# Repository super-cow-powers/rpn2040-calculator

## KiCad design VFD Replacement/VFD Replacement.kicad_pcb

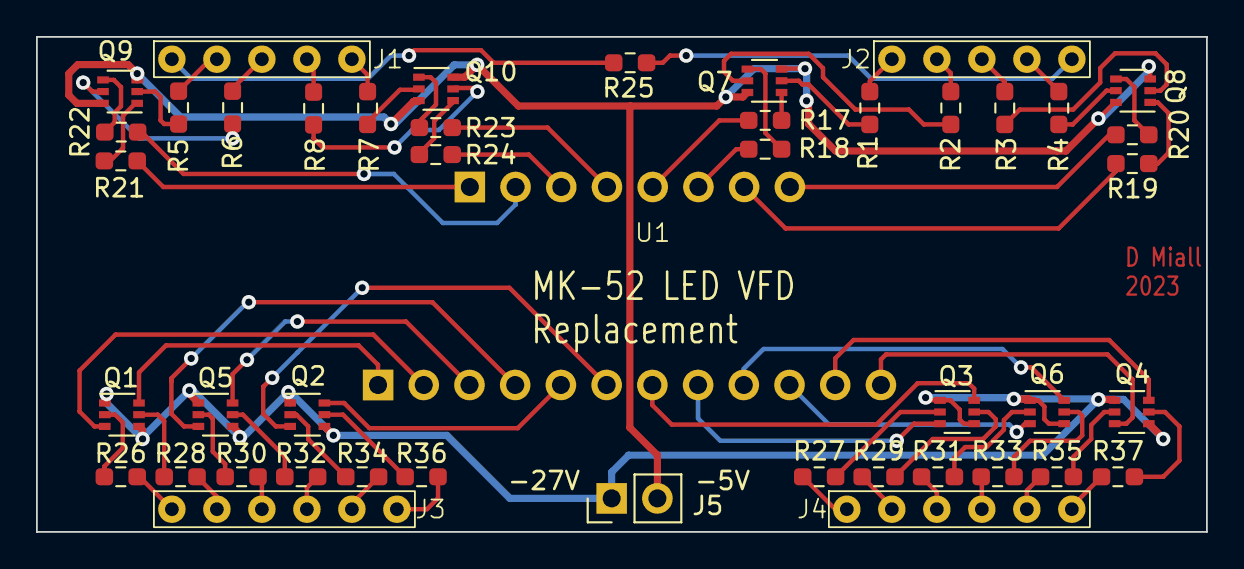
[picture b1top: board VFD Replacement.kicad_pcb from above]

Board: 2 copper layers, 65.0 x 27.5 mm, 45 parts (0 on the bottom side), 72 nets.

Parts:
J1, J2: Conn_01x05_Pin; Conn_1x05 2.5mm
J3, J4: Conn_01x06_Pin; Conn_1x06 2.5mm
J5: Conn_01x02_Pin; PinHeader_1x02_P2.54mm_Vertical
Q1, Q2, Q3, Q4, Q5, Q6, Q7, Q8, Q9, Q10: MMDT2222A; SOT-363_SC-70-6
R1, R2, R3, R4, R5, R6, R7, R8, R25: 12k; R_0603_1608Metric_Pad0.98x0.95mm_HandSolder
R17, R18, R19, R20, R21, R22, R23, R24: 2k4; R_0603_1608Metric_Pad0.98x0.95mm_HandSolder
R26, R27, R28, R29, R30, R31, R32, R33, R34, R35, R36, R37: 56k; R_0603_1608Metric_Pad0.98x0.95mm_HandSolder
U1: display

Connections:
+22V: J5.2, Q7.3 (C2), Q7.6 (C1), Q8.3 (C2), Q8.6 (C1), Q9.3 (C2), Q9.6 (C1), Q10.3 (C2), Q10.6 (C1)
-27V: J5.1, Q1.1 (E1), Q1.4 (E2), Q2.1 (E1), Q2.4 (E2), Q3.1 (E1), Q3.4 (E2), Q4.1 (E1), Q4.4 (E2), Q5.1 (E1), Q5.4 (E2), Q6.1 (E1), Q6.4 (E2)
/A: J2.1, R1.2
/As: R17.1, U1.5 (A)
/B: J2.2, R2.1
/Bs: R18.1, U1.6 (B)
/C: J2.3, R3.1
/Cs: R19.1, U1.7 (C)
/D: J1.2, R5.1
/DP: J2.4, R4.1
/DPs: R20.1, U1.8 (DP)
/Ds: R21.1, U1.1 (D)
/E: J1.3, R6.1
/Es: R22.1, U1.2 (E)
/F: J1.5, R7.1
/Fil A: J1.1, R25.2
/Fil B: J2.5, R25.1
/Fs: R23.1, U1.4 (F)
/G: J1.4, R8.1
/G1: J3.1, R26.1
/G1s: Q1.6 (C1), U1.9 (G1)
/G2: J3.2, R28.1
/G2s: Q1.3 (C2), U1.10 (G2)
/G3: J3.3, R30.1
/G3s: Q5.6 (C1), U1.11 (G3)
/G4: J3.4, R32.1
/G4s: Q5.3 (C2), U1.12 (G4)
/G5: J3.5, R34.1
/G5s: Q2.6 (C1), U1.13 (G5)
/G6: J3.6, R36.1
/G6s: Q2.3 (C2), U1.14 (G6)
/G7: J4.1, R27.1
/G7s: Q3.6 (C1), U1.15 (G7)
/G8: J4.2, R29.1
/G8s: Q3.3 (C2), U1.16 (G8)
/G9: J4.3, R31.1
/G9s: Q6.6 (C1), U1.17 (G9)
/G10: J4.4, R33.1
/G10s: Q6.3 (C2), U1.18 (G10)
/G11: J4.5, R35.1
/G11s: Q4.6 (C1), U1.19 (G11)
/G12: J4.6, R37.1
/G12s: Q4.3 (C2), U1.20 (G12)
/Gs: R24.1, U1.3 (G)
unnamed: Q1.2 (B1), R26.2
unnamed: Q1.5 (B2), R28.2
unnamed: Q2.2 (B1), R34.2
unnamed: Q2.5 (B2), R36.2
unnamed: Q3.2 (B1), R27.2
unnamed: Q3.5 (B2), R29.2
unnamed: Q4.2 (B1), R35.2
unnamed: Q4.5 (B2), R37.2
unnamed: Q5.2 (B1), R30.2
unnamed: Q5.5 (B2), R32.2
unnamed: Q6.2 (B1), R31.2
unnamed: Q6.5 (B2), R33.2
unnamed: Q7.2 (B1), R1.1
unnamed: Q7.1 (E1), R17.2
unnamed: Q7.5 (B2), R2.2
unnamed: Q7.4 (E2), R18.2
unnamed: Q8.2 (B1), R3.2
unnamed: Q8.1 (E1), R19.2
unnamed: Q8.5 (B2), R4.2
unnamed: Q8.4 (E2), R20.2
unnamed: Q9.2 (B1), R5.2
unnamed: Q9.1 (E1), R21.2
unnamed: Q9.5 (B2), R6.2
unnamed: Q9.4 (E2), R22.2
unnamed: Q10.2 (B1), R7.2
unnamed: Q10.1 (E1), R23.2
unnamed: Q10.5 (B2), R8.2
unnamed: Q10.4 (E2), R24.2

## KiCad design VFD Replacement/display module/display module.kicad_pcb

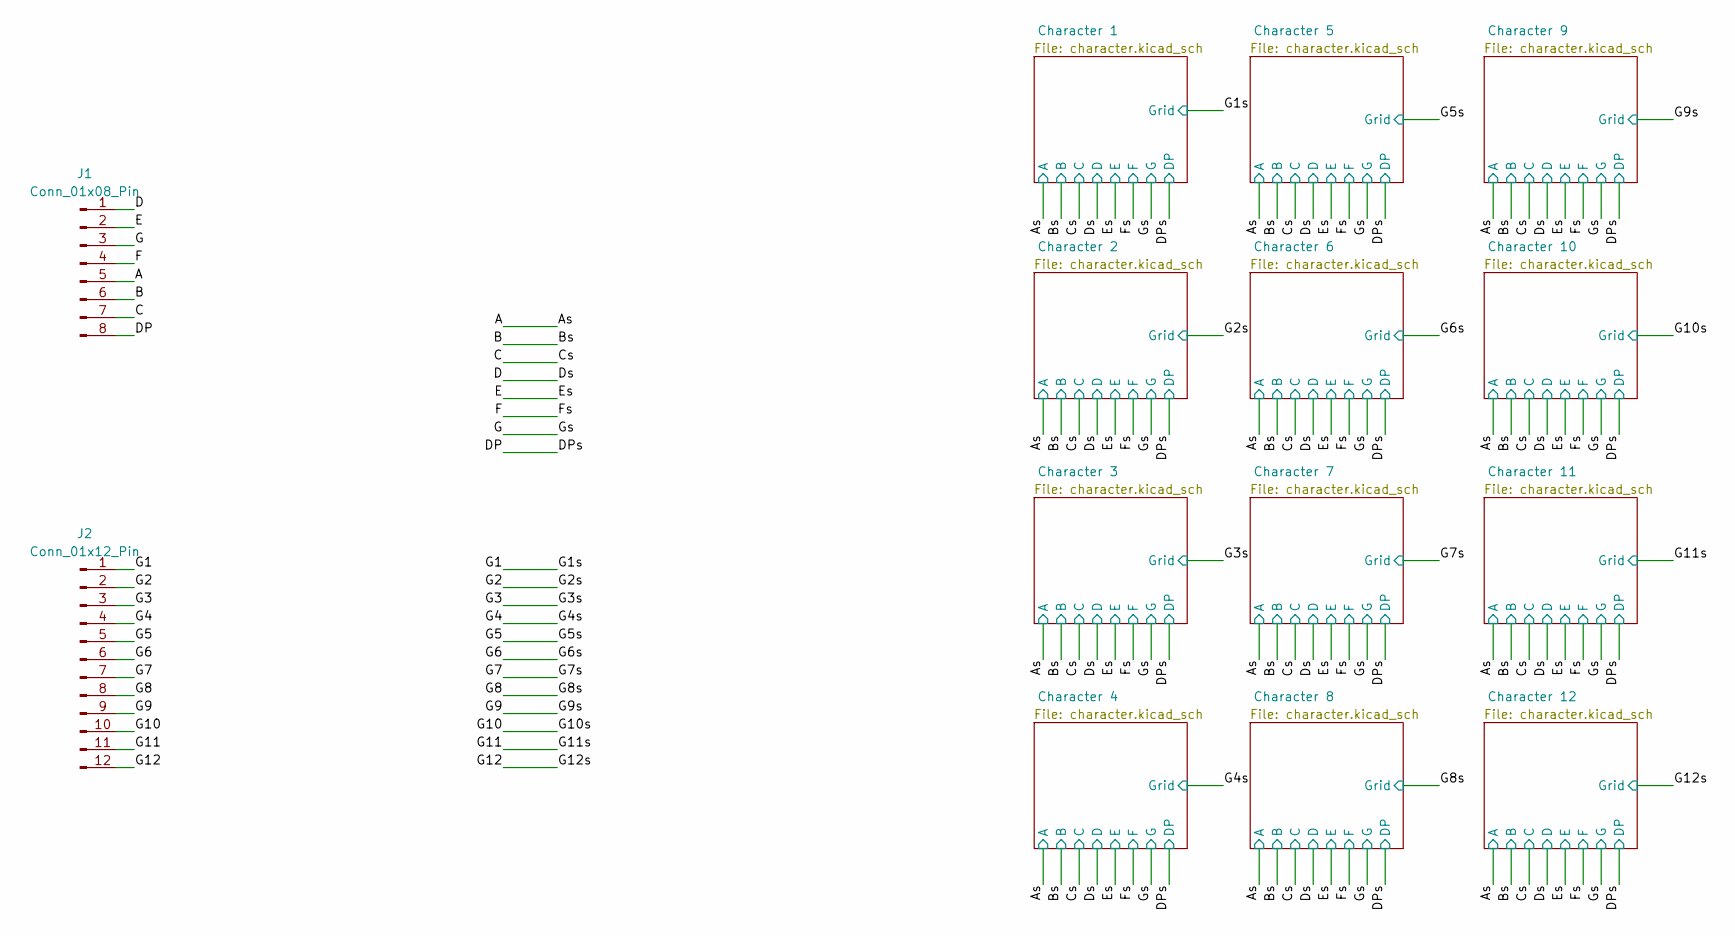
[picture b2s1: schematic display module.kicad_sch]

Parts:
J1: Conn_01x08_Pin; PinHeader_1x08_P2.54mm_Vertical
J2: Conn_01x12_Pin; PinHeader_1x12_P2.54mm_Vertical

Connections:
/A: J1.5; also elsewhere on the board
/B: J1.6; also elsewhere on the board
/C: J1.7; also elsewhere on the board
/D: J1.1; also elsewhere on the board
/DP: J1.8; also elsewhere on the board
/E: J1.2; also elsewhere on the board
/F: J1.4; also elsewhere on the board
/G: J1.3; also elsewhere on the board
/G1: J2.1; also elsewhere on the board
/G2: J2.2; also elsewhere on the board
/G3: J2.3; also elsewhere on the board
/G4: J2.4; also elsewhere on the board
/G5: J2.5; also elsewhere on the board
/G6: J2.6; also elsewhere on the board
/G7: J2.7; also elsewhere on the board
/G8: J2.8; also elsewhere on the board
/G9: J2.9; also elsewhere on the board
/G10: J2.10; also elsewhere on the board
/G11: J2.11; also elsewhere on the board
/G12: J2.12; also elsewhere on the board

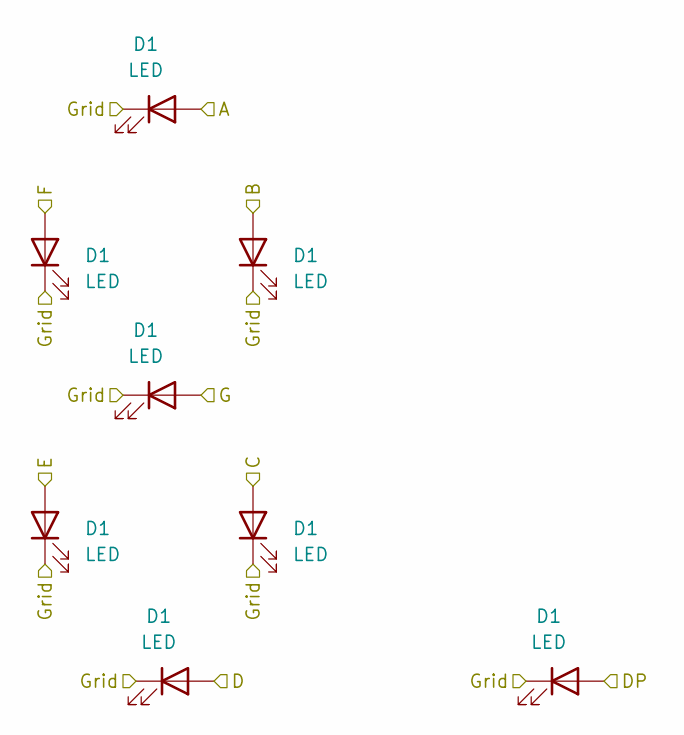
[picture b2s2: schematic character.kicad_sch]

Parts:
D1: LED; LED_0402_1005Metric

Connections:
/A: D1.2 (A); also elsewhere on the board
/G1: D1.1 (K); also elsewhere on the board

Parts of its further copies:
D2, D3, D4, D5, D6, D7, D8, D9, D10, D11, D12, D13, D14, D15, D16, D17, D18, D19, D20, D21, D22, D23, D24, D25, D26, D27, D28, D29, D30, D31, D32, D33, D34, D35, D36, D37, D38, D39, D40, D41, D42, D43, D44, D45, D46, D47, D48, D49, D50, D51, D52, D53, D54, D55, D56, D57, D58, D59, D60, D61, D62, D63, D64, D65, D66, D67, D68, D69, D70, D71, D72, D73, D74, D75, D76, D77, D78, D79, D80, D81, D82, D83, D84, D85, D86, D87, D88, D89, D90, D91, D92, D93, D94, D95, D96: LED; LED_0402_1005Metric

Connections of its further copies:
/A: D11.2 (A), D19.2 (A), D27.2 (A), D35.2 (A), D43.2 (A), D51.2 (A), D59.2 (A), D67.2 (A), D75.2 (A), D83.2 (A), D91.2 (A); also elsewhere on the board
/B: D6.2 (A), D14.2 (A), D22.2 (A), D30.2 (A), D38.2 (A), D46.2 (A), D54.2 (A), D62.2 (A), D70.2 (A), D78.2 (A), D86.2 (A), D94.2 (A); also elsewhere on the board
/C: D7.2 (A), D15.2 (A), D23.2 (A), D31.2 (A), D39.2 (A), D47.2 (A), D55.2 (A), D63.2 (A), D71.2 (A), D79.2 (A), D87.2 (A), D95.2 (A); also elsewhere on the board
/D: D4.2 (A), D13.2 (A), D21.2 (A), D29.2 (A), D37.2 (A), D45.2 (A), D53.2 (A), D61.2 (A), D69.2 (A), D77.2 (A), D85.2 (A), D93.2 (A); also elsewhere on the board
/DP: D8.2 (A), D16.2 (A), D24.2 (A), D32.2 (A), D40.2 (A), D48.2 (A), D56.2 (A), D64.2 (A), D72.2 (A), D80.2 (A), D88.2 (A), D96.2 (A); also elsewhere on the board
/E: D3.2 (A), D10.2 (A), D18.2 (A), D26.2 (A), D34.2 (A), D42.2 (A), D50.2 (A), D58.2 (A), D66.2 (A), D74.2 (A), D82.2 (A), D90.2 (A); also elsewhere on the board
/F: D2.2 (A), D9.2 (A), D17.2 (A), D25.2 (A), D33.2 (A), D41.2 (A), D49.2 (A), D57.2 (A), D65.2 (A), D73.2 (A), D81.2 (A), D89.2 (A); also elsewhere on the board
/G: D5.2 (A), D12.2 (A), D20.2 (A), D28.2 (A), D36.2 (A), D44.2 (A), D52.2 (A), D60.2 (A), D68.2 (A), D76.2 (A), D84.2 (A), D92.2 (A); also elsewhere on the board
/G1: D2.1 (K), D3.1 (K), D4.1 (K), D5.1 (K), D6.1 (K), D7.1 (K), D8.1 (K); also elsewhere on the board
/G2: D9.1 (K), D10.1 (K), D11.1 (K), D12.1 (K), D13.1 (K), D14.1 (K), D15.1 (K), D16.1 (K); also elsewhere on the board
/G3: D17.1 (K), D18.1 (K), D19.1 (K), D20.1 (K), D21.1 (K), D22.1 (K), D23.1 (K), D24.1 (K); also elsewhere on the board
/G4: D25.1 (K), D26.1 (K), D27.1 (K), D28.1 (K), D29.1 (K), D30.1 (K), D31.1 (K), D32.1 (K); also elsewhere on the board
/G5: D33.1 (K), D34.1 (K), D35.1 (K), D36.1 (K), D37.1 (K), D38.1 (K), D39.1 (K), D40.1 (K); also elsewhere on the board
/G6: D41.1 (K), D42.1 (K), D43.1 (K), D44.1 (K), D45.1 (K), D46.1 (K), D47.1 (K), D48.1 (K); also elsewhere on the board
/G7: D49.1 (K), D50.1 (K), D51.1 (K), D52.1 (K), D53.1 (K), D54.1 (K), D55.1 (K), D56.1 (K); also elsewhere on the board
/G8: D57.1 (K), D58.1 (K), D59.1 (K), D60.1 (K), D61.1 (K), D62.1 (K), D63.1 (K), D64.1 (K); also elsewhere on the board
/G9: D65.1 (K), D66.1 (K), D67.1 (K), D68.1 (K), D69.1 (K), D70.1 (K), D71.1 (K), D72.1 (K); also elsewhere on the board
/G10: D73.1 (K), D74.1 (K), D75.1 (K), D76.1 (K), D77.1 (K), D78.1 (K), D79.1 (K), D80.1 (K); also elsewhere on the board
/G11: D81.1 (K), D82.1 (K), D83.1 (K), D84.1 (K), D85.1 (K), D86.1 (K), D87.1 (K), D88.1 (K); also elsewhere on the board
/G12: D89.1 (K), D90.1 (K), D91.1 (K), D92.1 (K), D93.1 (K), D94.1 (K), D95.1 (K), D96.1 (K); also elsewhere on the board

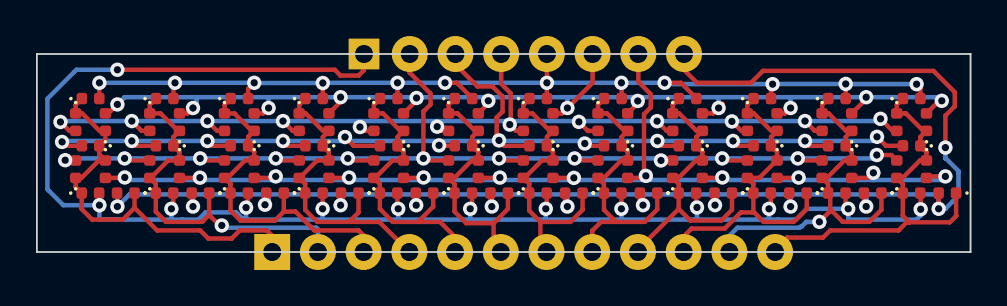
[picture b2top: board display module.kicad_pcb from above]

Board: 2 copper layers, 51.9 x 11.0 mm, 98 parts (0 on the bottom side), 20 nets.

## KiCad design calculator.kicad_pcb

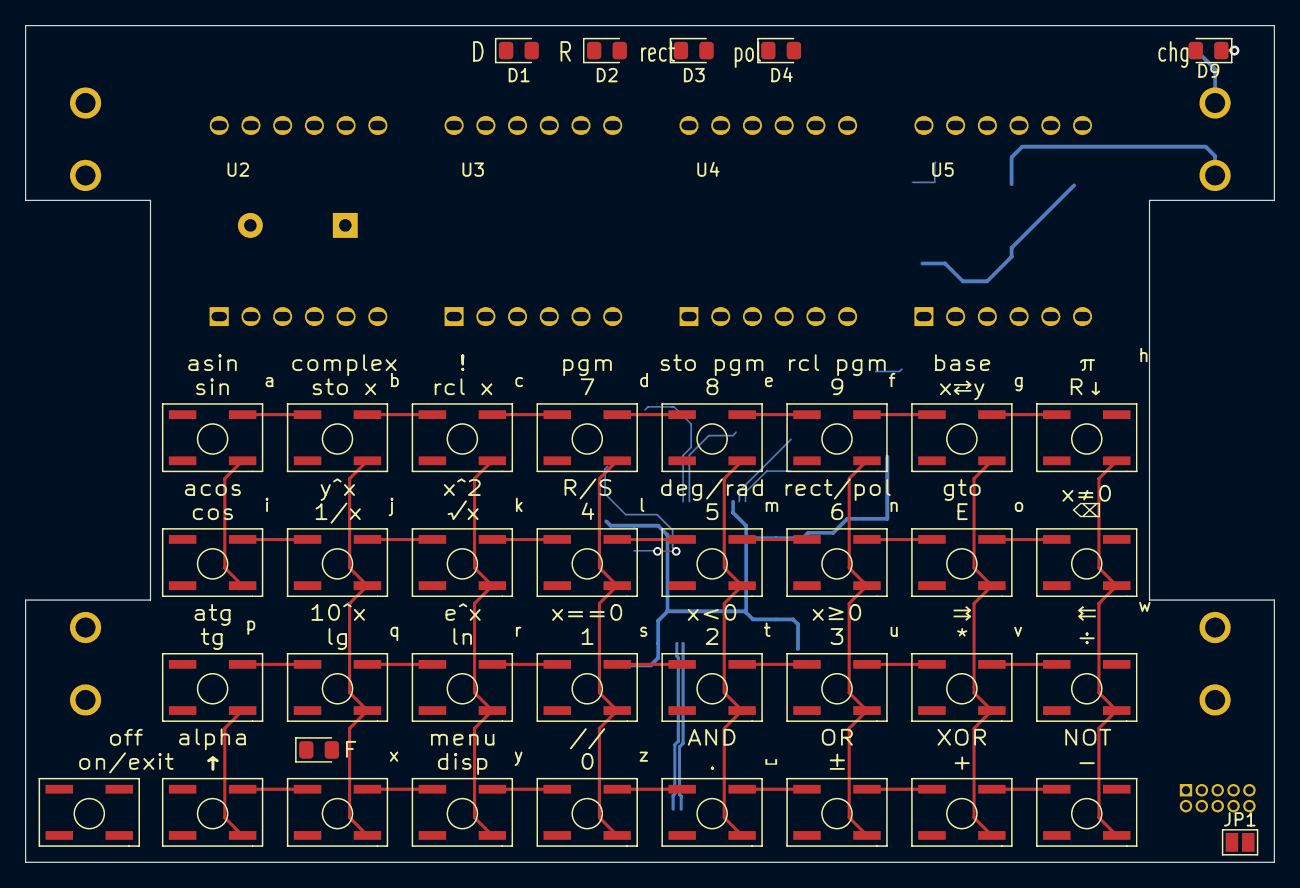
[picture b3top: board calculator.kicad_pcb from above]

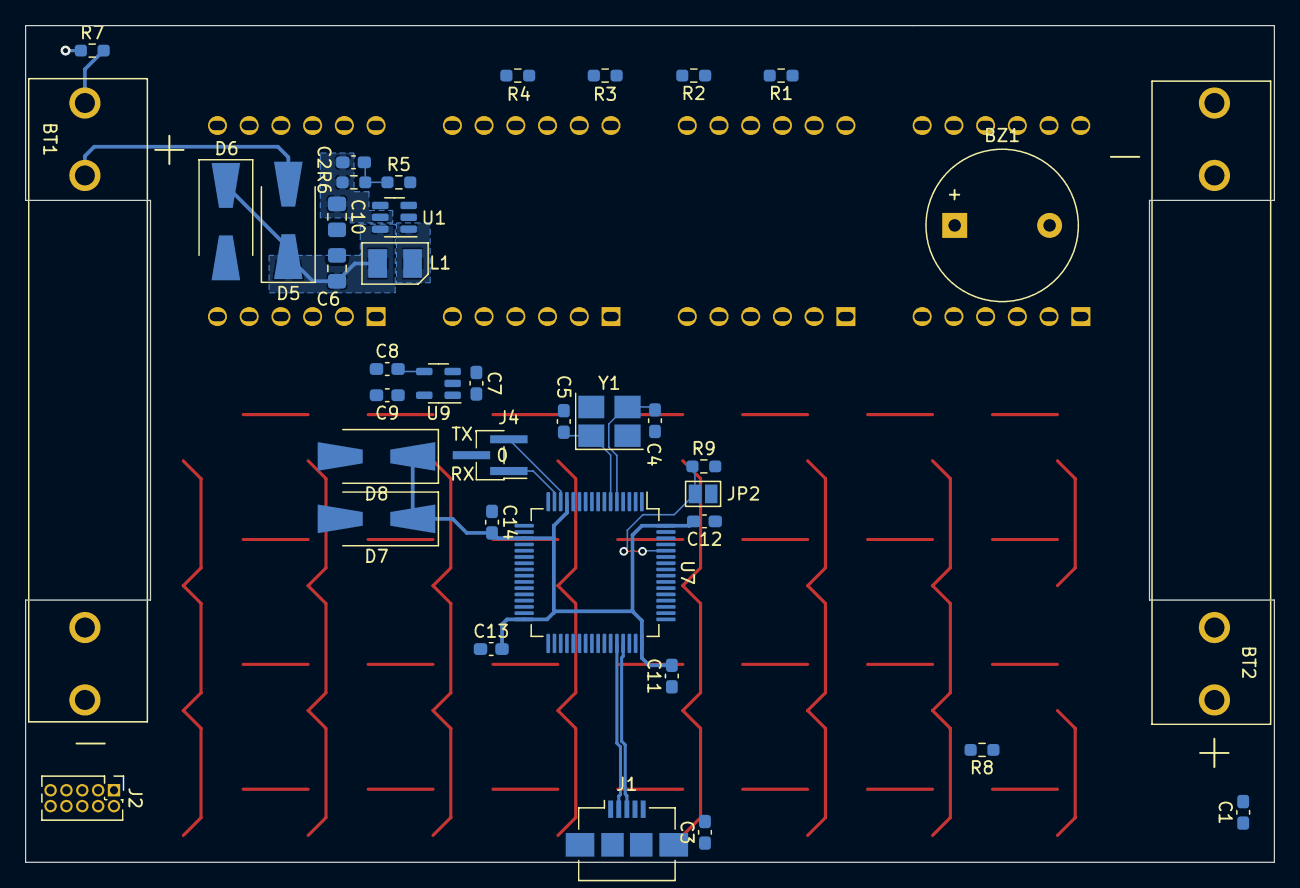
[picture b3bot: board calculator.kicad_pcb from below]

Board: 2 copper layers, 100.0 x 67.0 mm, 83 parts (39 on the bottom side), 59 nets.

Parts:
BT1, BT2: AA; Keystone 92 pair
BZ1: Buzzer; Buzzer_12x9.5RM7.6
C1: 10n; C_0603_1608Metric_Pad1.08x0.95mm_HandSolder
C2: DNF; C_0603_1608Metric_Pad1.08x0.95mm_HandSolder
C3: C; C_0603_1608Metric_Pad1.08x0.95mm_HandSolder
C4, C5: 16p; C_0603_1608Metric_Pad1.08x0.95mm_HandSolder
C6, C10: 10u; C_0805_2012Metric_Pad1.18x1.45mm_HandSolder
C7, C9: 2.2u; C_0603_1608Metric_Pad1.08x0.95mm_HandSolder
C8, C11, C12, C13, C14: .1u; C_0603_1608Metric_Pad1.08x0.95mm_HandSolder
D1, D2, D3, D4, D9, D10: LED; LED_0805_2012Metric_Pad1.15x1.40mm_HandSolder
D5, D6, D7, D8: SS14W; D_SMA-SMB_Universal_Handsoldering
J1: USB_B_Micro; USB_Micro-B_Amphenol_10104110_Horizontal
J2: Conn_ARM_JTAG_SWD_10; PinHeader_2x05_P1.27mm_Vertical
J4: Conn_01x03_Pin; PinHeader_1x03_P1.27mm_Vertical_SMD_Pin1Left
JP1, JP2: SolderJumper_2_Open; SolderJumper-2_P1.3mm_Open_Pad1.0x1.5mm
L1: HPC 5040NF-4R7M; HPC-BM
R1, R2, R3, R4, R8: 200; R_0603_1608Metric_Pad0.98x0.95mm_HandSolder
R5: 75k; R_0603_1608Metric_Pad0.98x0.95mm_HandSolder
R6: 680k; R_0603_1608Metric_Pad0.98x0.95mm_HandSolder
R7: 120; R_0603_1608Metric_Pad0.98x0.95mm_HandSolder
R9: 10k; R_0603_1608Metric_Pad0.98x0.95mm_HandSolder
SW1, SW2, SW3, SW4, SW5, SW6, SW7, SW8, SW9, SW10, SW11, SW12, SW13, SW14, SW16, SW17, SW18, SW19, SW20, SW21, SW22, SW23, SW24, SW25, SW26, SW27, SW28, SW29, SW30, SW31, SW32: SW_Push; PTS526
SW15: SW1; PTS526
SWON_OFF1: SW_Push; PTS526
U1: TLV61070A; SOT-23-6
U2, U3, U4, U5: HPDL1414; HPDLDL-1414
U7: STM32L476RCT6; LQFP-64_10x10mm_P0.5mm
U9: AP2210K-3.3TRG1; SOT-23-5
Y1: RH100-24.000-8-1015-EXT-TR-NS1; Crystal_SMD_3225-4Pin_3.2x2.5mm_HandSoldering

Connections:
+3V3: C9.1, D8.2 (A), J2.1 (VTref), U9.5 (VOUT)
+5V: C2.1, C7.1, C10.1, D1.2 (A), D2.2 (A), D3.2 (A), D4.2 (A), D10.2 (A), R6.1, U1.5 (VOUT), U2.6 (VDD), U3.6 (VDD), U4.6 (VDD), U5.6 (VDD), U9.1 (VIN), U9.3 (EN)
+BATT: BT1.1 (+), D6.2 (A), D7.2 (A), R7.2, U7.1 (VBAT)
/5vEN: U1.3 (EN), U7.17 (PA3)
/A0: U2.5 (A0), U3.5 (A0), U4.5 (A0), U5.5 (A0), U7.2 (PC13)
/A1: U2.4 (A1), U3.4 (A1), U4.4 (A1), U5.4 (A1), U7.3 (PC14)
/D0: U2.8 (D0), U3.8 (D0), U4.8 (D0), U5.8 (D0), U7.37 (PC6)
/D1: U2.9 (D1), U3.9 (D1), U4.9 (D1), U5.9 (D1), U7.38 (PC7)
/D2: U2.10 (D2), U3.10 (D2), U4.10 (D2), U5.10 (D2), U7.39 (PC8)
/D3: U2.11 (D3), U3.11 (D3), U4.11 (D3), U5.11 (D3), U7.40 (PC9)
/D4: U2.2 (D4), U3.2 (D4), U4.2 (D4), U5.2 (D4), U7.51 (PC10)
/D5: U2.1 (D5), U3.1 (D5), U4.1 (D5), U5.1 (D5), U7.52 (PC11)
/D6: U2.12 (D6), U3.12 (D6), U4.12 (D6), U5.12 (D6), U7.53 (PC12)
/DISP0: U2.3 (WR), U7.8 (PC0)
/DISP1: U3.3 (WR), U7.9 (PC1)
/DISP2: U4.3 (WR), U7.10 (PC2)
/DISP3: U5.3 (WR), U7.11 (PC3)
/Keys/K1: SW1.1, SW2.1, SW3.1, SW4.1, U7.56 (PB4)
/Keys/K2: SW5.1, SW6.1, SW7.1, SW8.1, U7.57 (PB5)
/Keys/K3: SW9.1, SW10.1, SW11.1, SW12.1, U7.58 (PB6)
/Keys/K4: SW13.1, SW14.1, SW15.1, SW16.1, U7.59 (PB7)
/Keys/K5: SW17.1, SW18.1, SW19.1, SW20.1, U7.61 (PB8)
/Keys/K6: SW21.1, SW22.1, SW23.1, SW24.1, U7.62 (PB9)
/Keys/K7: SW25.1, SW26.1, SW27.1, SW28.1, U7.29 (PB10)
/Keys/K8: SW29.1, SW30.1, SW31.1, SW32.1, U7.30 (PB11)
/Keys/R1: SW1.2, SW5.2, SW9.2, SW13.2, SW17.2, SW21.2, SW25.2, SW29.2, U7.26 (PB0)
/Keys/R2: SW2.2, SW6.2, SW10.2, SW14.2, SW18.2, SW22.2, SW26.2, SW30.2, U7.27 (PB1)
/Keys/R3: SW3.2, SW7.2, SW11.2, SW15.2, SW19.2, SW23.2, SW27.2, SW31.2, U7.28 (PB2)
/Keys/R4: SW4.2, SW8.2, SW12.2, SW16.2, SW20.2, SW24.2, SW28.2, SW32.2, U7.55 (PB3)
/LD1: R1.2, U7.20 (PA4)
/LD2: R2.2, U7.21 (PA5)
/LD3: R3.2, U7.22 (PA6)
/LD4: R4.2, U7.23 (PA7)
/LD5: R8.2, U7.41 (PA8)
/Power/BATT/2: BT1.2 (-), BT2.1 (+)
/Power/SMPS_IN: C6.1, D5.1 (K), D6.1 (K), L1.2, U1.6 (VIN)
/Power/SMPS_SW: L1.1, U1.1 (SW)
/USART4_RX: J4.1, U7.15 (PA1)
/USART4_TX: J4.3, U7.14 (PA0)
/USB_D+: J1.3 (D+), U7.45 (PA12)
/USB_D-: J1.2 (D-), U7.44 (PA11)
/VDD_MCU: C11.2, C12.2, C13.2, C14.2, D7.1 (K), D8.1 (K), JP2.2 (B), U7.13 (VDDA), U7.19 (VDD), U7.32 (VDD), U7.48 (VDDUSB), U7.64 (VDD)
/rst: J2.10 (~RESET), JP1.2 (B), U7.7 (NRST)
GND: BT2.2 (-), BZ1.2 (+), C1.2, C3.2, C4.1, C5.2, C6.2, C7.2, C8.1, C9.2, C10.2, C11.1, C12.1, C13.1, C14.1, J1.5 (GND), J2.3 (GND), J2.5 (GND), J4.2, JP1.1 (A), R5.2, R9.2, SWON_OFF1.2, U1.2 (GND), U2.7 (GND), U3.7 (GND), U4.7 (GND), U5.7 (GND), U7.12 (VSSA), U7.18 (VSS), U7.31 (VSS), U7.47 (VSS), U7.63 (VSS), U9.2 (GND), Y1.2, Y1.4
unnamed: BZ1.1 (-), U7.16 (PA2)
unnamed: D1.1 (K), R1.1
unnamed: D2.1 (K), R2.1
unnamed: D3.1 (K), R3.1
unnamed: D4.1 (K), R4.1
unnamed: D9.1 (K), R7.1
unnamed: D10.1 (K), R8.1
unnamed: C3.1, J1.6 (Shield)
unnamed: JP2.1 (A), R9.1, U7.60 (BOOT0)
unnamed: C2.2, R5.1, R6.2, U1.4 (FB)
unnamed: C1.1, SWON_OFF1.1, U7.33 (PB12)
unnamed: C4.2, U7.5 (PH0), Y1.3
unnamed: C5.1, U7.6 (PH1), Y1.1
unnamed: C8.2, U9.4 (ADJ)
Vusb: D5.2 (A), D9.2 (A), J1.1 (VBUS)

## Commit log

2023-11-05 Init
2023-11-05 Add ROM driver sheet
2023-11-06 Begin screen module
2023-11-12 Create Display PCB
2023-11-16 Update VFD Replacement layout
2023-11-17 Update lib
2023-11-17 Create display module
2023-11-17 Complete
2023-11-19 Check 7-seg module and VFD interposer. Create outputs
2023-11-19 Update outputs
2023-11-19 Update display base resistor values
2023-12-16 Update values from sim
2023-12-26 Add code
2023-12-26 Update code
